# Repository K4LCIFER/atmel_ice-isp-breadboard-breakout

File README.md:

# Atmel ICE ISP Breadboard Breakout

## Introduction

The purpose of this device is to facilitate the connection between an
[Atmel-ICE](https://www.microchip.com/DevelopmentTools/ProductDetails/atatmel-ice)
programmer and a breadboard.

<details> <summary>Click here to see more pictures</summary>

</details><!-- Perhaps I should do away with this section. -->

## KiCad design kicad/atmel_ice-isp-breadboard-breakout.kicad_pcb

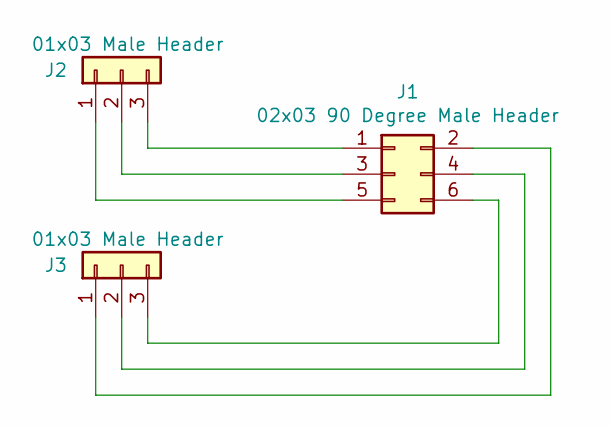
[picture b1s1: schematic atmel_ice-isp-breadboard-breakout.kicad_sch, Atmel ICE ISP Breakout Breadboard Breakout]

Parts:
J1: 02x03 90 Degree Male Header; PinHeader_2x03_P2.54mm_Horizontal
J2, J3: 01x03 Male Header; PinHeader_1x03_P2.54mm_Vertical

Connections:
unnamed: J1.1, J2.3
unnamed: J1.2, J3.1
unnamed: J1.3, J2.2
unnamed: J1.4, J3.2
unnamed: J1.5, J2.1
unnamed: J1.6, J3.3

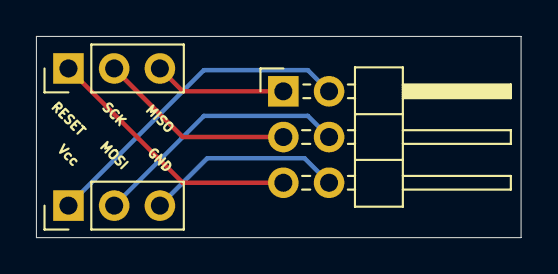
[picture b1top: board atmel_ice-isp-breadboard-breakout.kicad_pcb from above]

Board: 2 copper layers, 26.9 x 11.2 mm, 3 parts (0 on the bottom side), 6 nets.

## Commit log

2021-07-20 Initial commit.
2021-07-21 Added an introduction to the README. TODO: needs a "usage" section.
2021-07-31 Renamed the folder holding the kicad files to 'kicad'
2021-07-31 Added pictures of breakout for the README
2021-07-31 Added 3 IRL images to the README.
2021-07-31 Temporararily removed collapsible details section for images, as they were having issues displaying.
2021-07-31 Added pictures of basic PCB renders, and added them to the README. Changed the layout of some pictures in the README.
2021-08-07 Updated .gitignore to the standard github kicad gitignore.
